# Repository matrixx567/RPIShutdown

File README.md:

RPIShutdown
===========

RPIShutdown adds a power switch to the Raspberry Pi. So it is possible to completely 
disconnect the Pi from the electrical power source.

How it works?
-------------
It works in the same way as the power button in the desktop computer will do.

Usually the Raspberry Pi isn't powered. If the button is pressed, the Raspberry Pi will be started.
The next press will smoothly shutdown the PI by running the `halt` command.  
If you press the button for about 4 seconds the Raspberry Pi will be hardly shutdown by 
disconnecting the power.

Installation
-------------
More information is available in the [installation notes](http://rpishutdown.readthedocs.org/content/installation-notes.html) in the documentation.

Documentation
--------------
More information are available in the [project documentation](http://rpishutdown.readthedocs.org).

other Projects
--------------

[ATXRaspi](http://lowpowerlab.com/atxraspi/): Has nearly the same functionality and you can buy it. 
But it isn't open source.

[PI2RMini](https://awjlogan.wordpress.com/2014/03/01/pi2rmini-a-proper-power-switch-for-the-raspberrypi/)

License
--------------
The MIT License (MIT)

Copyright (c) 2013 Martin Noehrer

Permission is hereby granted, free of charge, to any person obtaining a copy of
this software and associated documentation files (the "Software"), to deal in
the Software without restriction, including without limitation the rights to
use, copy, modify, merge, publish, distribute, sublicense, and/or sell copies of
the Software, and to permit persons to whom the Software is furnished to do so,
subject to the following conditions:

The above copyright notice and this permission notice shall be included in all
copies or substantial portions of the Software.

THE SOFTWARE IS PROVIDED "AS IS", WITHOUT WARRANTY OF ANY KIND, EXPRESS OR
IMPLIED, INCLUDING BUT NOT LIMITED TO THE WARRANTIES OF MERCHANTABILITY, FITNESS
FOR A PARTICULAR PURPOSE AND NONINFRINGEMENT. IN NO EVENT SHALL THE AUTHORS OR
COPYRIGHT HOLDERS BE LIABLE FOR ANY CLAIM, DAMAGES OR OTHER LIABILITY, WHETHER
IN AN ACTION OF CONTRACT, TORT OR OTHERWISE, ARISING FROM, OUT OF OR IN
CONNECTION WITH THE SOFTWARE OR THE USE OR OTHER DEALINGS IN THE SOFTWARE.

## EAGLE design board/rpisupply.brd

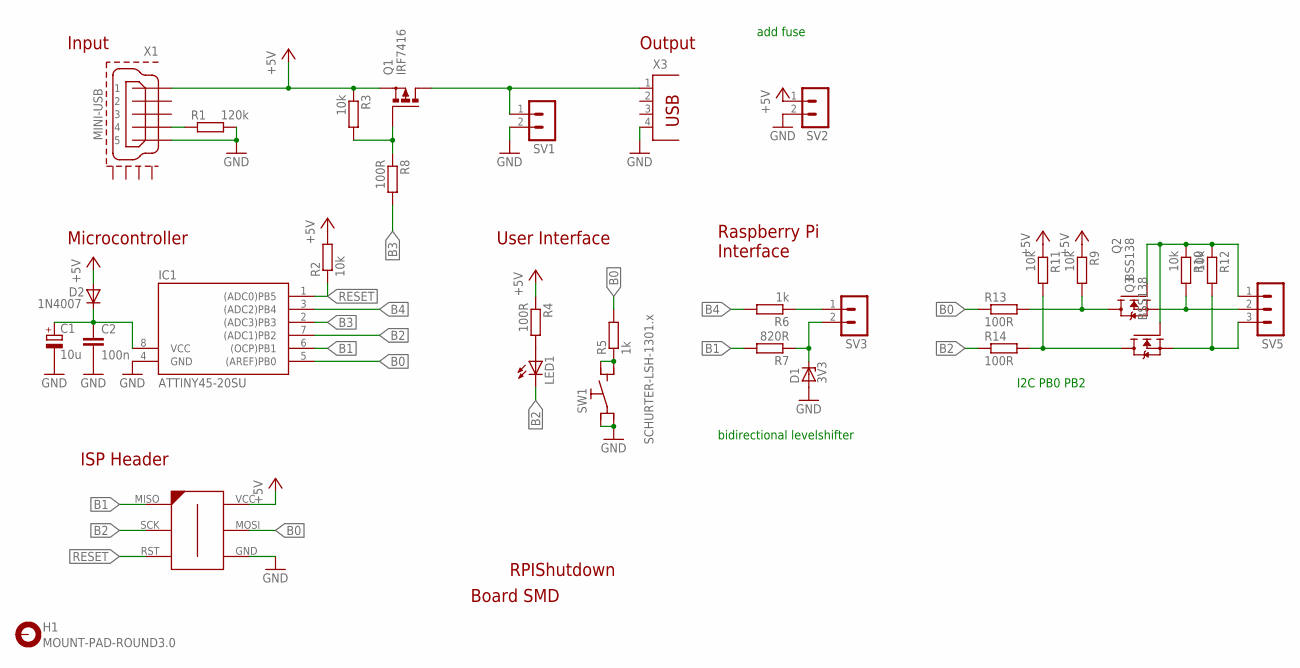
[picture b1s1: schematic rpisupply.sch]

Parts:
C1: 10u; SMC_C
C2: 100n; C0805
D1: 3V3; SOD80C
D2: 1N4007; MELF-MLL41
H1: MOUNT-PAD-ROUND3.0; 3,0-PAD
IC1: ATTINY45-20SU; SOIC8
LED1: LEDSML0805; SML0805
Q1: IRF7416; SO-08
Q2, Q3: BSS138; SOT23
R1: 120k; R0805
R2, R3, R9, R10, R11, R12: 10k; R0805
R4, R8, R13, R14: 100R; R0805
R5, R6: 1k; R0805
R7: 820R; R0805
SV1, SV2, SV3: MA02-1R; MA02-1
SV5: MA03-1R; MA03-1
SW1: SCHURTER-LSH-1301.x; LSH
X1: MINI-USB; UX60-MB-5ST
X2: AVR-ISP-6-EDGE; 6PAD_ISP
X3: PN87520

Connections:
+5V: D2.A, Q1.1 (S), Q1.2 (S), Q1.3 (S), R2.2, R3.1, R4.1, R9.1, R11.1, SV2.1, X1.1, X2.VCC
B0: IC1.5 ((AREF)PB0), R5.2, R13.1, X2.MOSI
B1: IC1.6 ((OCP)PB1), R7.2, X2.MISO
B2: IC1.7 ((ADC1)PB2), LED1.C, R14.1, X2.SCK
B3: IC1.2 ((ADC3)PB3), R8.2
B4: IC1.3 ((ADC2)PB4), R6.2
GND: C1.-, C2.2, D1.A, IC1.4 (GND), R1.2, SV1.2, SV2.2, SW1.C1 (C), SW1.C2 (C), X1.5, X2.GND, X3.4
unnamed: R6.1, SV3.1
unnamed: D1.C, R7.1, SV3.2
unnamed: R1.1, X1.4
unnamed: LED1.A, R4.2
unnamed: R5.1, SW1.NO1 (NO), SW1.NO2 (NO)
unnamed: Q1.4 (G), R3.2, R8.1
unnamed: C1.+, C2.1, D2.C, IC1.8 (VCC)
unnamed: Q2.1 (G), Q3.1 (G), R10.1, R12.1, SV5.1
unnamed: Q2.2 (S), R10.2, SV5.2
unnamed: Q3.3 (D), R11.2, R14.2
unnamed: Q3.2 (S), R12.2, SV5.3
unnamed: Q2.3 (D), R9.2, R13.2
unnamed: Q1.5 (D), Q1.6 (D), Q1.7 (D), Q1.8 (D), SV1.1, X3.1
RESET: IC1.1 ((ADC0)PB5), R2.1, X2.RST

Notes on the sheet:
RPIShutdown
Board SMD
ISP Header
Microcontroller
Raspberry Pi Interface
User Interface
Input
Output
bidirectional levelshifter
I2C PB0 PB2
add fuse

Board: 2 copper layers, 32 parts (0 on the bottom side), 21 nets, no tracks yet.

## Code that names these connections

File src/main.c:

/************************************************************************
Project:  RPISupply
Title:    Add a supply switch to the raspberry pi
Author:   Martin Noehrer
Email:    matrixx567@yahoo.at
Homepage: https://github.com/matrixx567/RPIShutdown
File:     main.c
Date:

License:  MIT License

LICENSE:
Copyright (C) 2013 Martin Noehrer

Permission is hereby granted, free of charge, to any person obtaining a 
copy of this software and associated documentation files (the "Software"),
to deal in the Software without restriction, including without limitation 
the rights to use, copy, modify, merge, publish, distribute, sublicense, 
and/or sell copies of the Software, and to permit persons to whom the 
Software is furnished to do so, subject to the following conditions:
The above copyright notice and this permission notice shall be included 
in all copies or substantial portions of the Software.

THE SOFTWARE IS PROVIDED "AS IS", WITHOUT WARRANTY OF ANY KIND, EXPRESS 
OR IMPLIED, INCLUDING BUT NOT LIMITED TO THE WARRANTIES OF MERCHANTABILITY,
FITNESS FOR A PARTICULAR PURPOSE AND NONINFRINGEMENT. IN NO EVENT SHALL THE 
AUTHORS OR COPYRIGHT HOLDERS BE LIABLE FOR ANY CLAIM, DAMAGES OR OTHER 
LIABILITY, WHETHER IN AN ACTION OF CONTRACT, TORT OR OTHERWISE, ARISING 
FROM, OUT OF OR IN CONNECTION WITH THE SOFTWARE OR THE USE OR OTHER 
DEALINGS IN THE SOFTWARE.
 *************************************************************************
Software: WIN-AVR 20100110 - AVR-GCC 4.3.3, AVR Libc 1.6.7
Hardware: ATtiny45 at 8Mhz /DIV8 => 1MHz
Fuses:    LFUSE:62 HFUSE:DF EFUSE:FF
Fuses:    LFUSE:62 HFUSE:DD EFUSE:FF	new Setting
Usage:
 *************************************************************************
Pin Description:
B0: inp	Switch		 low...pressed
B1:	out	RPI-TX		 output to raspberrypi
B2:	out	Status-LED   low...LED on
B3:	out	Relay		 high...on
B4:	inp	RPI-RX		 input from raspberrypi
 *************************************************************************
Description: see documentation
 *************************************************************************
Changelog:
 *************************************************************************
contains code and ideas from:
 ************************************************************************/


 // #define USE_MOSFET

//internal 8MHz oscillator with CKDIV8
#ifndef F_CPU
#define F_CPU 1000000UL     /* 1 Mhz internal oscillator  */
#endif


#include <avr/io.h>
#include <avr/sleep.h>
#include <avr/interrupt.h>
#include <util/delay.h>


#define IRPIRX	PB4
#define ORELAY	PB3
#define OLED	PB2
#define ORPITX	PB1
#define ISWITCH	PB0


#ifdef USE_MOSFET
// use mosfet - active low
	#define RELAY_ON	PORTB &= ~(1<<ORELAY)
	#define RELAY_OFF	PORTB |= (1<<ORELAY)
#else
// use relay - active high
	#define RELAY_ON	PORTB |= (1<<ORELAY)
	#define RELAY_OFF	PORTB &= ~(1<<ORELAY)
#endif


//internal states
enum sm_states_e {
	POWER_OFF = 0,
	STARTUP,
	RUNNING,
	SHUTDOWN
};


// modes for the LED
enum led_mode_e {
	LED_OFF=0,
	LED_BLINKING,
	LED_ON
};


// states of the button
enum button_state_e{
	NO_PRESS = 0,
	SHORT_PRESS,
	LONG_PRESS
};

// counter for button's debouncing and for detecting the long press
volatile uint16_t button_cnt = 0;

// counter for detecting the delay timer overflows
volatile uint8_t delay_counter = 0;

// actual mode of the LED
volatile enum led_mode_e led_mode = LED_OFF;


/**
 * Interrupt service routine for Timer 0.
 *
 * This timer is used to detect a long press of the button
 */
ISR( TIMER0_OVF_vect )                   // every 16ms
{
	button_cnt++;
}

/**
 * Interrupt service routine for Timer 1.
 *
 * This timer is used to generate delay functionality.
 */
ISR(TIMER1_OVF_vect) {				//every 500ms
	if(led_mode == LED_BLINKING)
		PORTB ^= (1<<OLED);
	delay_counter++;
}


ISR(INT0_vect) {

}

ISR(PCINT0_vect) {

}



int main(void) {

	//internal actual state of the state machine
	enum sm_states_e states_e = POWER_OFF;

	//actual state of the button
	enum button_state_e buttonstate = NO_PRESS;

	//temporary state which is used for resetting the delay counter
	enum sm_states_e temp_states_e = POWER_OFF;


	//set direction of pins to output
	DDRB = (1 << ORELAY) | (1 << OLED) | (1 << ORPITX);

	RELAY_OFF;		//Switch off relay

	PORTB &= ~(1<<ORPITX);		//Switch off TX


	// Configure debouncing routines
	DDRB  &= ~(1<<ISWITCH);                // configure key port for input
	PORTB |= (1<<ISWITCH);                // and turn on pull up resistors

	TCCR0B = (1<<CS01)|(1<<CS00);         // divide by 64
	// overflow 0.016 sec

	TIMSK |= 1<<TOIE0;                   // enable timer interrupt

	TCCR1 |= (1<<CS13) |(1<<CS12); // Prescaler 2048
	// overflow time about 0.5 sec

	PCMSK |= (1<<PCINT0); //  tell pin change mask to listen to PB0, Switch
	PCMSK |= (1<<PCINT4); //  tell pin change mask to listen to PB4, RPIInput

	// Overflow Interrupt erlauben
	TIMSK |= (1<<TOIE1);
	GIMSK |= (1<<PCIE);
	sei();

	set_sleep_mode(SLEEP_MODE_PWR_DOWN);


	//Detecting reset of microcontroller - for debugging
	PORTB &= ~(1<<OLED);
	for(int i=0; i < 10 ; i++){
		PORTB ^= 1<<OLED;
		_delay_ms(100);
	}
	PORTB |= (1<<OLED);


	while (1) {



		buttonstate=NO_PRESS;

		if( !(PINB & (1<<ISWITCH )) ) {
			button_cnt=0;
			while(button_cnt < 6){	//wait for about 50ms - debouncing
			}
			while(!(PINB & (1<<ISWITCH ))){
				buttonstate=SHORT_PRESS;
				if(button_cnt >= 250){	//4sec long button press-shutdown
					buttonstate=LONG_PRESS;
					break;
				}
			}
			button_cnt=0;
			while(button_cnt < 6){	//wait for about 50ms - debouncing
			}
		}


		temp_states_e = states_e;


		//state transition function
		switch(states_e) {
		case POWER_OFF:
			if ( SHORT_PRESS == buttonstate )
				states_e = STARTUP;
			break;
		case STARTUP:
			if( (PINB & (1<<IRPIRX)) && delay_counter >= 6 ) {
				states_e = RUNNING;
			}
			if( delay_counter >= 120 ) {
				states_e = RUNNING;
			}
			break;
		case RUNNING:
			if( !(PINB &(1<<IRPIRX))) {
				states_e = SHUTDOWN;
			}
			if( SHORT_PRESS == buttonstate ) {
				states_e = SHUTDOWN;
			}
			break;
		case SHUTDOWN:
			if( (PINB &(1<<IRPIRX)) && delay_counter >= 4 ) {
				states_e = RUNNING;
			}
			if((!(PINB &(1<<IRPIRX))) && delay_counter >= 40 ) {	//20sec
				states_e = POWER_OFF;
			}
			if( delay_counter >= 120 ) {
				states_e = POWER_OFF;
			}
			break;
		}


		if ( LONG_PRESS == buttonstate ) {
			states_e = POWER_OFF;
		}


		if( temp_states_e != states_e) {
			delay_counter = 0;
		}

		//output function
		switch(states_e) {
		case POWER_OFF:
			RELAY_OFF;
			PORTB &= ~(1<<ORPITX);		//Switch off TX
			led_mode = LED_OFF;
			break;
		case STARTUP:
			RELAY_ON;
			PORTB &= ~(1<<ORPITX);		//Switch off TX
			led_mode = LED_BLINKING;
			break;
		case RUNNING:
			RELAY_ON;
			PORTB &= ~(1<<ORPITX);		//Switch off TX
			led_mode = LED_ON;
			break;
		case SHUTDOWN:
			RELAY_ON ;
			PORTB |= (1<<ORPITX);		//Switch on TX
			led_mode = LED_BLINKING;
			break;
		}


		if(led_mode == LED_ON) {
			PORTB &= ~(1<<OLED);
		} else if (led_mode == LED_OFF) {
			PORTB |= (1<<OLED);
		}


		while(LONG_PRESS == buttonstate && (!(PINB & (1<<ISWITCH )))){	//if long button press
																//wait for release
		}



		cli();
		if (states_e == POWER_OFF || states_e == RUNNING) {
			sleep_enable();
			sei();
			sleep_cpu();
			sleep_disable();

			//sleep wakeup
			delay_counter = 0;
		}
		sei();


	}

	return 0;
}

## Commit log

2014-08-25 Repository reinitialization
2014-11-08 remove logo in doc
2015-02-13 Change docs to sphinx
2015-07-27 add images for documentation
2015-08-16 add PyCharm project files to gitignore
2015-08-16 remove local rtd sphinx theme
2015-08-16 remove old eclipse project after changing to AtmelStudio
2015-08-16 Remove napoleon from Sphinx Project
2015-08-16 Update Readme to ReadTheDocs
2015-08-18 update sphinx references
2015-10-04 Change email address within code header
2015-10-04 Change frame in schematics
2016-03-08 add bidirectional levelshifter
2016-03-08 update docs
2016-03-15 add components for next version
2016-03-18 change docs to mkdocs

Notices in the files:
parts and their libraries:
frames: CREATIVE COMMONS
